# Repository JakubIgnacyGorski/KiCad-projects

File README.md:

# KiCad-projects
My KiCad projects

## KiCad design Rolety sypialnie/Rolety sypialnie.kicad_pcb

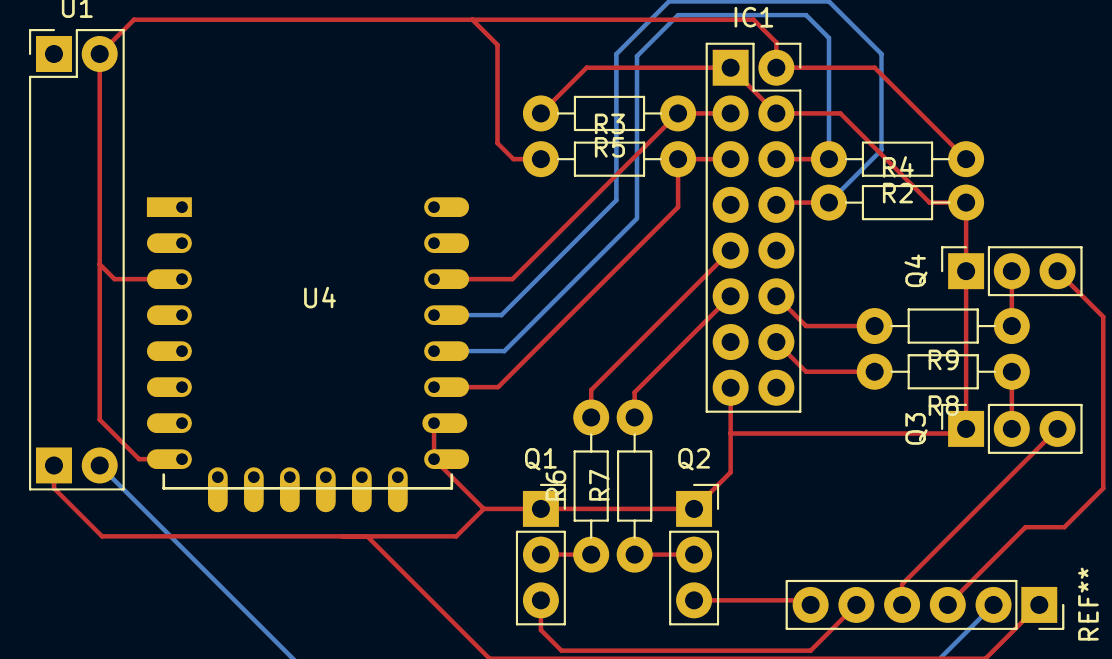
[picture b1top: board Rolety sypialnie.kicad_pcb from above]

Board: 2 copper layers, 15 parts (0 on the bottom side), 14 nets.

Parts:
IC1: CD4555BE
Q1, Q2, Q3, Q4: S9014 C331; PinSocket_1x03_P2.54mm_Vertical
R2, R3, R4, R5, R6, R7, R8, R9: 4k7; R_Axial_DIN0204_L3.6mm_D1.6mm_P7.62mm_Horizontal
U1: 5V to 3.3V; 5v to 3.3v
U4: ESP-12F; ESP-12E

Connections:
GND: IC1.1, IC1.8, IC1.15, Q1.1, Q2.1, Q3.1, Q4.1, R4.2, R5.2, U1.1, U4.15, U4.16
unnamed: IC1.2, R2.2, U4.18
unnamed: IC1.3, R4.1, U4.19
unnamed: IC1.5, R9.2
unnamed: IC1.6, R8.2
unnamed: IC1.10, R7.2
unnamed: IC1.11, R6.2
unnamed: IC1.13, R3.2, U4.17
unnamed: IC1.14, R5.1, U4.20
unnamed: IC1.16, R2.1, R3.1, U1.2, U4.3, U4.8
unnamed: Q1.2, R6.1
unnamed: Q2.2, R7.1
unnamed: Q3.2, R8.1
unnamed: Q4.2, R9.1

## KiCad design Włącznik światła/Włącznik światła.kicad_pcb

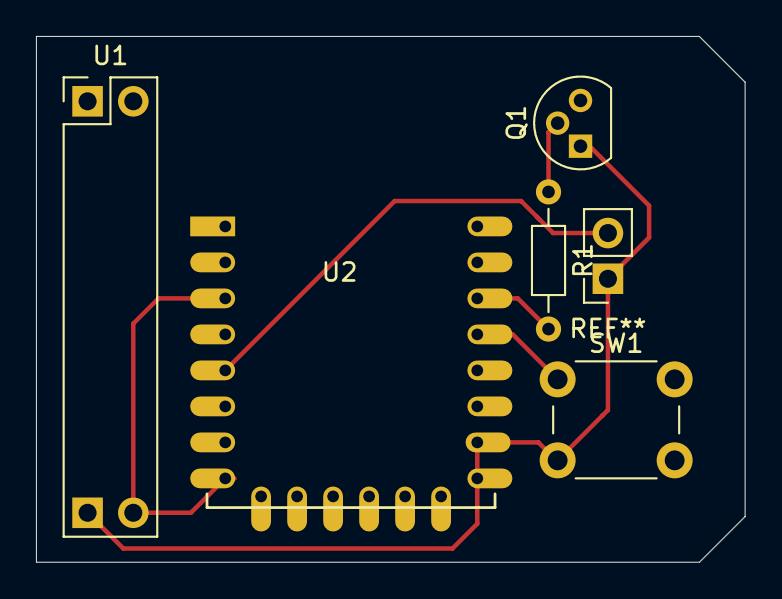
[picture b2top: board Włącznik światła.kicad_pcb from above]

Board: 2 copper layers, 39.4 x 29.2 mm, 5 parts (0 on the bottom side), 5 nets.

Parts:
Q1: 2N2222; TO-92L
R1: 4k7; R_Axial_DIN0204_L3.6mm_D1.6mm_P7.62mm_Horizontal
SW1: SW_Push; SW_PUSH_6mm
U1: 5v to 3.3v
U2: ESP-12E

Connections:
unnamed: Q1.1, SW1.2, U1.1, U2.15, U2.16
unnamed: Q1.2, R1.1
unnamed: R1.2, U2.20
unnamed: SW1.1, U2.19
unnamed: U1.3, U2.3, U2.8

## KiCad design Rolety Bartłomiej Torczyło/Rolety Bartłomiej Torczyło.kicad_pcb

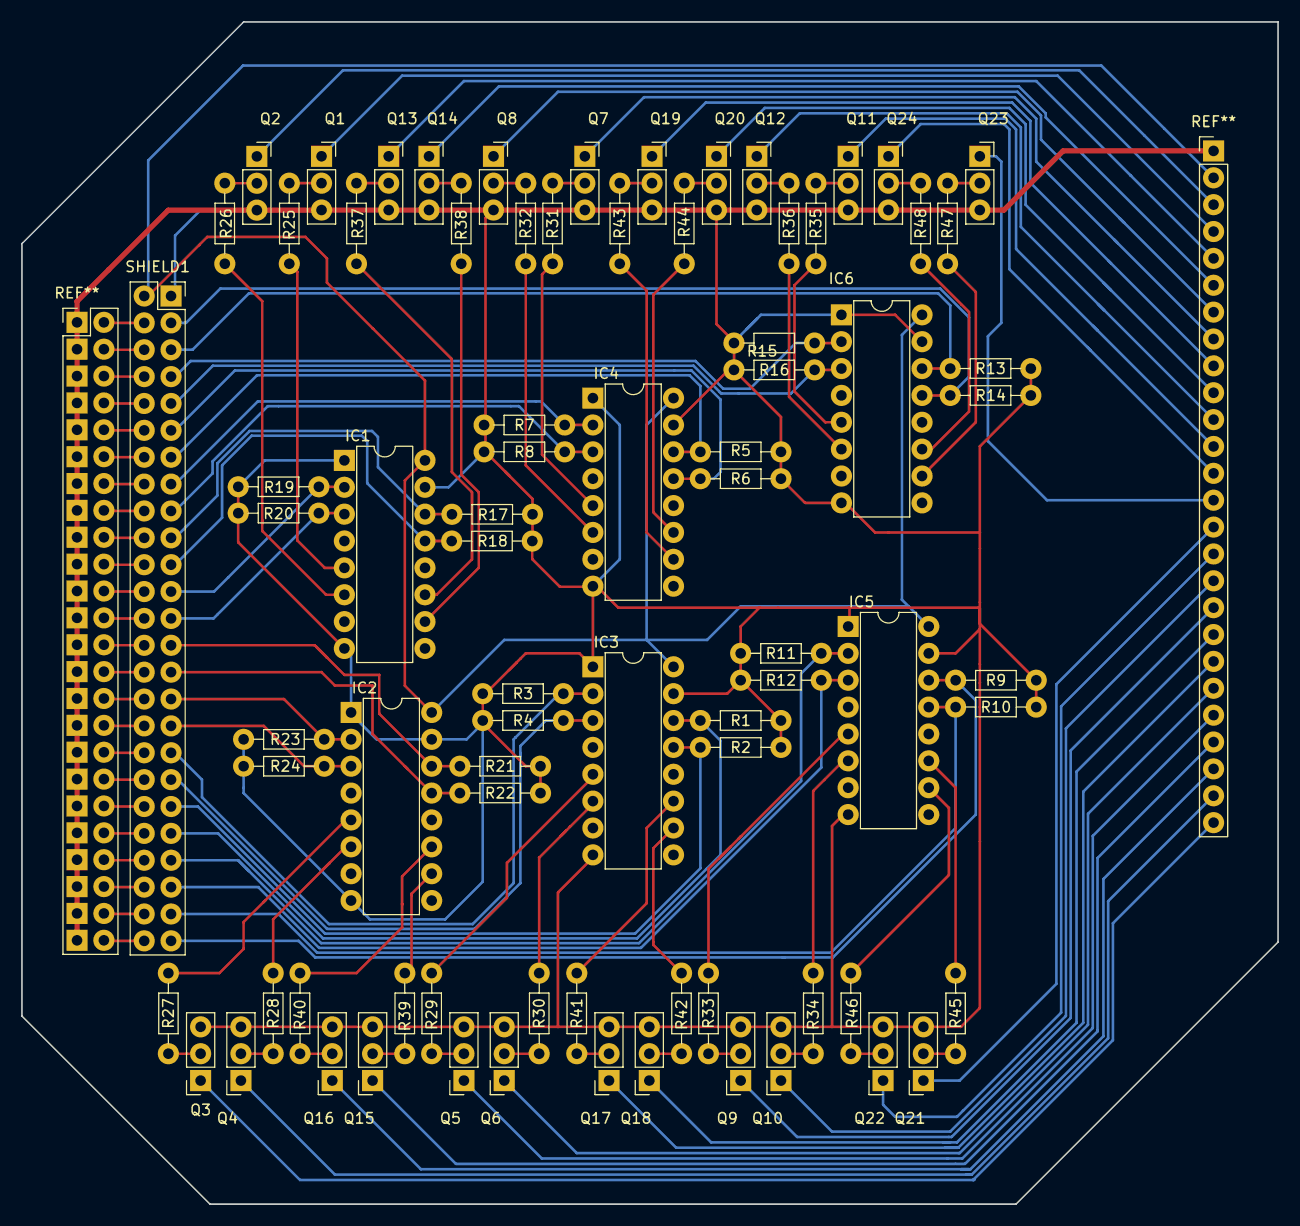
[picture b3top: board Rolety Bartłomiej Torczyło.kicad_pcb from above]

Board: 2 copper layers, 118.7 x 111.8 mm, 79 parts (0 on the bottom side), 74 nets.

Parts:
IC1, IC2, IC3, IC4, IC5, IC6: CD4555BE
Q1, Q2, Q3, Q4, Q5, Q6, Q7, Q8, Q9, Q10, Q11, Q12, Q13, Q14, Q15, Q16, Q17, Q18, Q19, Q20, Q21, Q22, Q23, Q24: S9018; PinSocket_1x03_P2.54mm_Vertical
R1, R2, R3, R4, R5, R6, R7, R8, R9, R10, R11, R12, R13, R14, R15, R16, R17, R18, R19, R20, R21, R22, R23, R24, R25, R26, R27, R28, R29, R30, R31, R32, R33, R34, R35, R36, R37, R38, R39, R40, R41, R42, R43, R44, R45, R46, R47, R48: 4k7; R_Axial_DIN0204_L3.6mm_D1.6mm_P7.62mm_Horizontal
SHIELD1: ARDUINO_MEGA_SHIELD; PinSocket_2x25_P2.54mm_Vertical

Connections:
unnamed: IC1.1, IC1.8, IC1.15, IC2.1, IC2.8, IC2.15, IC3.1, IC3.8, IC3.15, IC4.1, IC4.8, IC4.15, IC5.1, IC5.8, IC5.15, IC6.1, IC6.8, IC6.15, Q1.3, Q2.3, Q3.3, Q4.3, Q5.3, Q6.3, Q7.3, Q8.3, Q9.3, Q10.3, Q11.3, Q12.3, Q13.3, Q14.3, Q15.3, Q16.3, Q17.3, Q18.3, Q19.3, Q20.3, Q21.3, Q22.3, Q23.3, Q24.3, R1.2, R2.2, R3.2, R4.2, R5.2, R6.2, R7.2, R8.2, R9.2, R10.2, R11.2, R12.2, R13.2, R14.2, R15.2, R16.2, R17.2, R18.2, R19.2, R20.2, R21.2, R22.1, R23.2, R24.2, SHIELD1.1
unnamed: IC1.2, R19.1, SHIELD1.30
unnamed: IC1.3, R20.1, SHIELD1.31
unnamed: IC1.5, R25.2
unnamed: IC1.6, R26.2
unnamed: IC1.10, R38.2
unnamed: IC1.11, R37.2
unnamed: IC1.13, R18.1, SHIELD1.32
unnamed: IC1.14, R17.1, SHIELD1.33
unnamed: IC2.2, R23.1, SHIELD1.34
unnamed: IC2.3, R24.1, SHIELD1.35
unnamed: IC2.5, R27.2
unnamed: IC2.6, R28.2
unnamed: IC2.10, R39.2
unnamed: IC2.11, R40.2
unnamed: IC2.13, R22.2, SHIELD1.36
unnamed: IC2.14, R21.1, SHIELD1.37
unnamed: IC3.2, R3.1, SHIELD1.52
unnamed: IC3.3, R4.1, SHIELD1.53
unnamed: IC3.5, R29.2
unnamed: IC3.6, R30.2
unnamed: IC3.10, R42.2
unnamed: IC3.11, R41.2
unnamed: IC3.13, R2.1, SHIELD1.51
unnamed: IC3.14, R1.1, SHIELD1.50
unnamed: IC4.2, R7.1, SHIELD1.44
unnamed: IC4.3, R8.1, SHIELD1.45
unnamed: IC4.5, R31.2
unnamed: IC4.6, R32.2
unnamed: IC4.10, R43.2
unnamed: IC4.11, R44.2
unnamed: IC4.13, R6.1, SHIELD1.41
unnamed: IC4.14, R5.1, SHIELD1.40
unnamed: IC5.2, R11.1, SHIELD1.42
unnamed: IC5.3, R12.1, SHIELD1.43
unnamed: IC5.5, R33.2
unnamed: IC5.6, R34.2
unnamed: IC5.10, R46.2
unnamed: IC5.11, R45.2
unnamed: IC5.13, R10.1, SHIELD1.45
unnamed: IC5.14, R9.1, SHIELD1.44
unnamed: IC6.3, R16.1, SHIELD1.47
unnamed: IC6.2, R15.1, SHIELD1.46
unnamed: IC6.5, R35.1
unnamed: IC6.6, R36.1
unnamed: IC6.10, R47.1
unnamed: IC6.11, R48.1
unnamed: IC6.13, R14.1, SHIELD1.49
unnamed: IC6.14, R13.1, SHIELD1.48
unnamed: Q14.2, R38.1
unnamed: Q13.2, R37.1
unnamed: Q1.2, R25.1
unnamed: Q2.2, R26.1
unnamed: Q3.2, R27.1
unnamed: Q4.2, R28.1
unnamed: Q16.2, R40.1
unnamed: Q15.2, R39.1
unnamed: Q5.2, R29.1
unnamed: Q6.2, R30.1
unnamed: Q17.2, R41.1
unnamed: Q18.2, R42.1
unnamed: Q20.2, R44.1
unnamed: Q19.2, R43.1
unnamed: Q7.2, R31.1
unnamed: Q8.2, R32.1
unnamed: Q9.2, R33.1
unnamed: Q10.2, R34.1
unnamed: Q22.2, R46.1
unnamed: Q21.2, R45.1
unnamed: Q23.2, R47.2
unnamed: Q24.2, R48.2
unnamed: Q11.2, R35.2
unnamed: Q12.2, R36.2
unnamed: IC1.16, IC2.16, IC3.16, IC4.16, IC5.16, IC6.16, SHIELD1.2

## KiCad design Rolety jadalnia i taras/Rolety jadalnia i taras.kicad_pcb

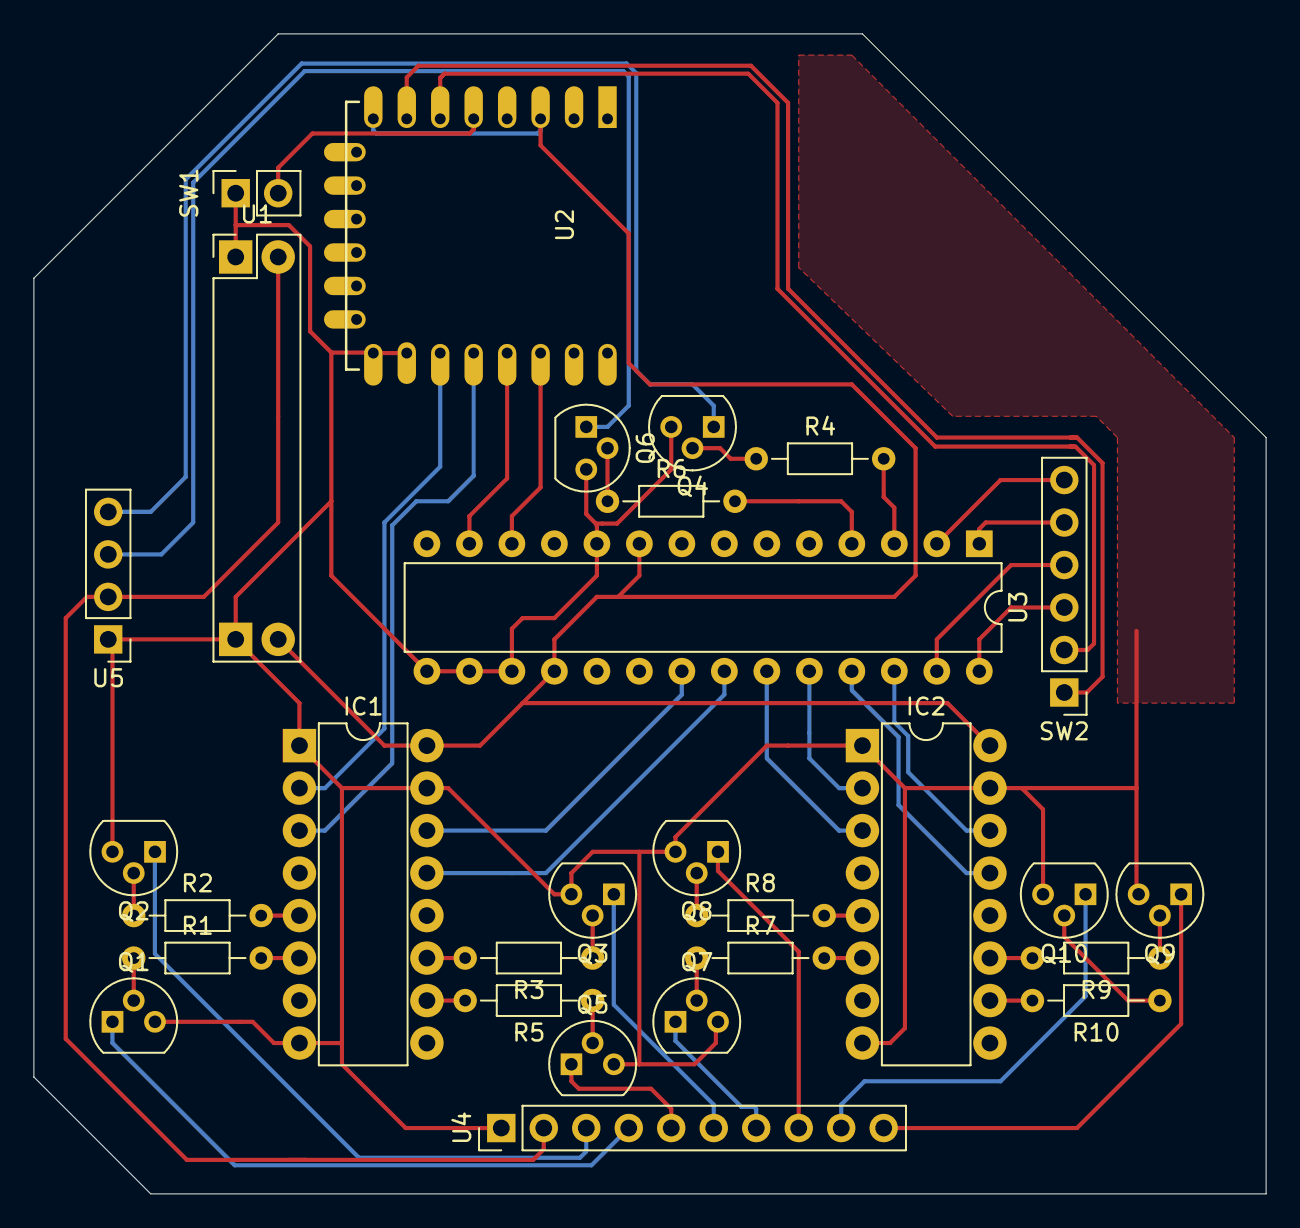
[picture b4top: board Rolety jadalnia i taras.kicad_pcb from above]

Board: 2 copper layers, 73.7 x 69.3 mm, 29 parts (0 on the bottom side), 50 nets.

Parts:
IC1, IC2: CD4555BE
Q1, Q2, Q3, Q4, Q5, Q6, Q7, Q8, Q9, Q10: 2N2222; TO-92
R1, R2, R3, R4, R5, R6, R7, R8, R9, R10: 4k7; R_Axial_DIN0204_L3.6mm_D1.6mm_P7.62mm_Horizontal
SW1: SW_Reed; PinSocket_1x02_P2.54mm_Vertical
SW2: SW_DIP_x06; PinHeader_1x06_P2.54mm_Vertical
U1: 5vto3.3v; 5v to 3.3v
U2: ESP-12E
U3: MCP23017_SO; DIP-28_W7.62mm
U4: 8x_Arduino_Relay_SSR; PinHeader_1x10_P2.54mm_Vertical
U5: Double_Arduino_Relay_SSR; PinHeader_1x04_P2.54mm_Vertical

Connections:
unnamed: IC1.1, IC1.8, IC1.15, IC2.1, IC2.8, IC2.15, Q1.3, Q2.3, Q3.3, Q4.3, Q5.3, Q6.3, Q7.3, Q8.3, Q9.3, Q10.3, SW1.1, U1.1, U2.15, U2.16, U3.10, U3.15, U3.16, U3.17, U4.1, U5.1
unnamed: IC1.3, U2.18
unnamed: IC1.2, U2.17
unnamed: IC1.5, R2.2
unnamed: IC1.6, R1.2
unnamed: IC1.10, R5.2
unnamed: IC1.11, R3.2
unnamed: IC1.13, U3.22
unnamed: IC1.14, U3.21
unnamed: IC1.16, IC2.16, U1.3, U2.3, U2.8, U3.9, U3.18
unnamed: IC2.2, U3.24
unnamed: IC2.3, U3.23
unnamed: IC2.5, R8.2
unnamed: IC2.6, R7.2
unnamed: IC2.10, R10.2
unnamed: IC2.11, R9.2
unnamed: IC2.13, U3.25
unnamed: IC2.14, U3.26
unnamed: Q1.1, U4.4
unnamed: Q1.2, R1.1
unnamed: Q2.1, U4.3
unnamed: Q2.2, R2.1
unnamed: Q3.1, U4.6
unnamed: Q3.2, R3.1
unnamed: Q4.1, U5.4
unnamed: Q4.2, R4.1
unnamed: Q5.1, U4.5
unnamed: Q5.2, R5.1
unnamed: Q6.1, U5.3
unnamed: Q6.2, R6.1
unnamed: Q7.1, U4.7
unnamed: Q7.2, R7.1
unnamed: Q8.1, U4.8
unnamed: Q8.2, R8.1
unnamed: Q9.1, U4.10
unnamed: Q9.2, R9.1
unnamed: Q10.1, U4.9
unnamed: Q10.2, R10.1
unnamed: R4.2, U3.3
unnamed: R6.2, U3.4
unnamed: SW1.2, U2.5
unnamed: SW2.1, U2.7
unnamed: SW2.2, U2.6
unnamed: SW2.3, U3.28
unnamed: SW2.4, U3.27
unnamed: SW2.5, U3.1
unnamed: SW2.6, U3.2
unnamed: U1.2, U4.2, U5.2
unnamed: U2.19, U3.13
unnamed: U2.20, U3.12

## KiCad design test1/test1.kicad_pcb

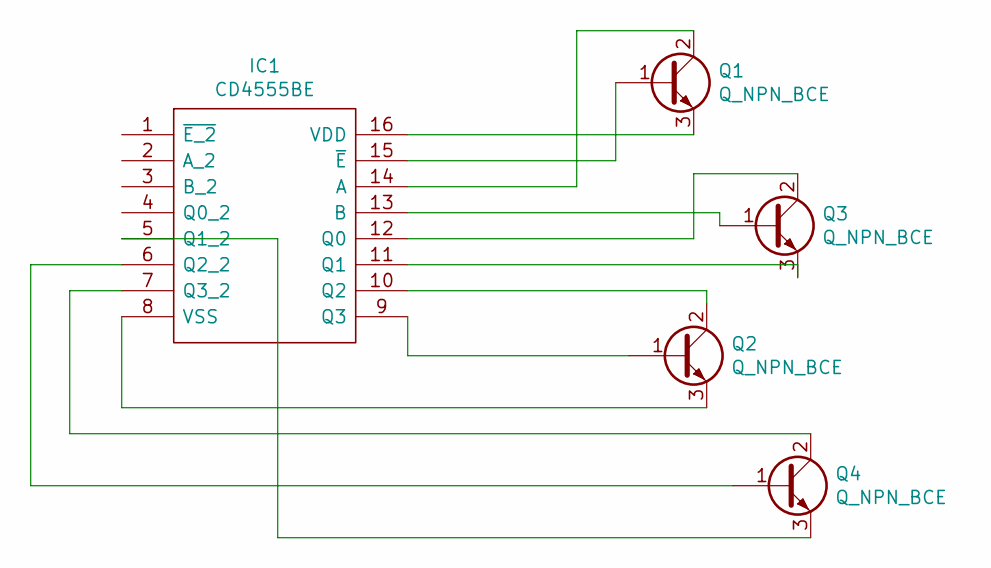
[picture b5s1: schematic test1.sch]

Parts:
IC1: CD4555BE; Manufacturer_Part_Number CD4555BE; Mouser Part Number 595-CD4555BE
Q1, Q2, Q3, Q4: Q_NPN_BCE; TO-92

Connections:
unnamed: IC1.5 (Q1_2), Q4.3 (E)
unnamed: IC1.6 (Q2_2), Q4.1 (B)
unnamed: IC1.7 (Q3_2), Q4.2 (C)
unnamed: IC1.8 (VSS), Q2.3 (E)
unnamed: IC1.9 (Q3), Q2.1 (B)
unnamed: IC1.10 (Q2), Q2.2 (C)
unnamed: IC1.11 (Q1), Q3.3 (E)
unnamed: IC1.12 (Q0), Q3.2 (C)
unnamed: IC1.13 (B), Q3.1 (B)
unnamed: IC1.14 (A), Q1.2 (C)
unnamed: IC1.15 (~E), Q1.1 (B)
unnamed: IC1.16 (VDD), Q1.3 (E)

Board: 2 copper layers, 5 parts (0 on the bottom side), 12 nets, no tracks yet.

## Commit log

2021-07-20 Cleaning
2021-08-16 Create fp-info-cache
2021-08-16 Logic gates
    Simulated not tested
2021-08-17 Strych board v0.1
